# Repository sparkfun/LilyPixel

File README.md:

LilyPad Pixel Board
===================

[*LilyPad Pixel Board (DEV-13264)*](https://www.sparkfun.com/products/13264)

This is a sewable single RGB LEDThe pixel board is equipped with a WS2812. This is an RGB LED with an WS2811 built right into the LED. 
These can be chained together to form a display or an addressable string. 

Repository Contents
-------------------
* **/Hardware** - All Eagle design files (.brd, .sch)
* **/Production** - Test bed files and production panel files

Product Versions
----------------
* [DEV-13264](https://www.sparkfun.com/products/13264)- Version 1.1. Currently live. 
* [DEV-11891](https://www.sparkfun.com/products/11891)- Version 1.0. Retired.

Version History
---------------
* [V_1.1](https://github.com/sparkfun/LilyPixel/tree/V_1.1) - GitHub files version 1.1
* [V_1.0](https://github.com/sparkfun/LilyPixel/tree/V_1.0) - GitHub files version 1.0

License Information
-------------------

This product is _**open source**_! 

Please review the LICENSE.md file for license information. 

If you have any questions or concerns on licensing, please contact techsupport@sparkfun.com.

Distributed as-is; no warranty is given.

- Your friends at SparkFun.

_**Note:** A portion of this sale is given back to Dr. Leah Buechley for continued development and education of e-textiles._

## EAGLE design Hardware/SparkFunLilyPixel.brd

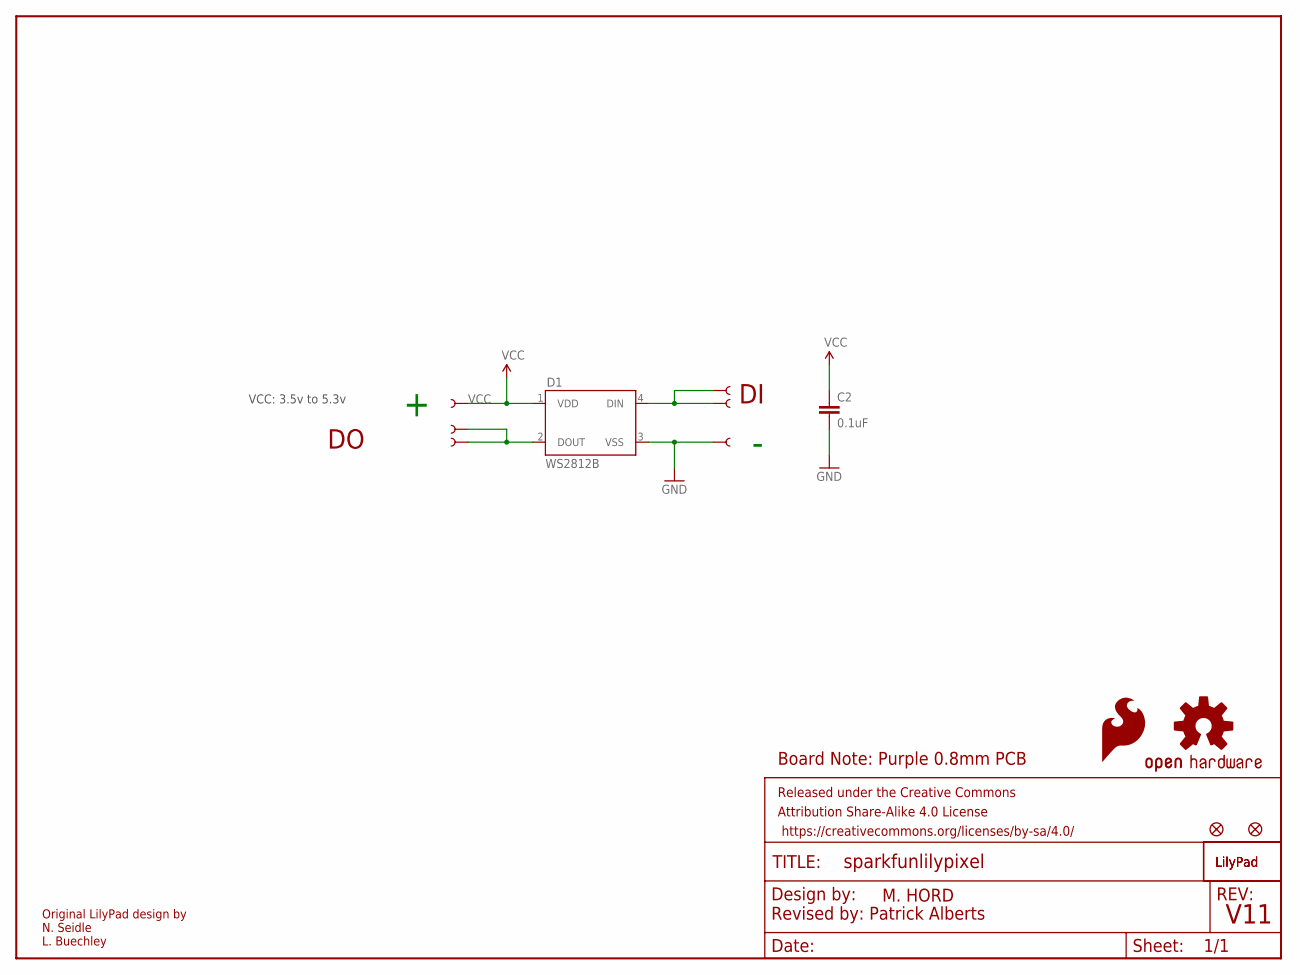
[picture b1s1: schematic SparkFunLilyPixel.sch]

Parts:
C2: 0.1uF; 0603-CAP
D1: WS2812B
FID1, FID2: FIDUCIAL1X2; FIDUCIAL-1X2
FRAME1: FRAME-LETTER; CREATIVE_COMMONS
JP1, JP2, JP3, JP4, JP5, JP6: SEWTAP6; PETAL-SMALL-2SIDE
LOGO1: OSHW-LOGOS; OSHW-LOGO-S
LOGO2: SFE_LOGO_FLAME.1_INCH; SFE_LOGO_FLAME_.1
U$1: LOGO-LPLP; LOGO-LILYPAD
U$8: LOGO-LPL; LOGO-L

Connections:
DI1: D1.4 (DIN), JP5.1, JP6.1
DO1: D1.2 (DOUT), JP1.1, JP2.1
GND: C2.2, D1.3 (VSS), JP3.1
VCC: C2.1, D1.1 (VDD), JP4.1

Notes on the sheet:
M. HORD
V11
Original LilyPad design by N. Seidle L. Buechley
Revised by: Patrick Alberts
VCC: 3.5v to 5.3v
Board Note: Purple 0.8mm PCB

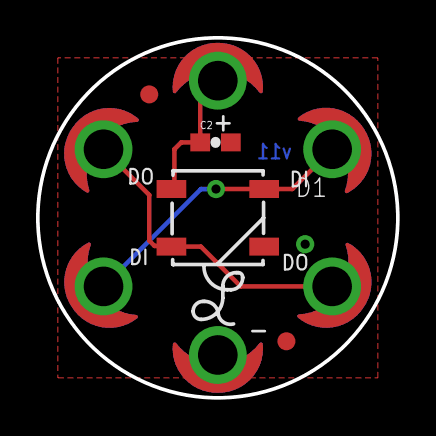
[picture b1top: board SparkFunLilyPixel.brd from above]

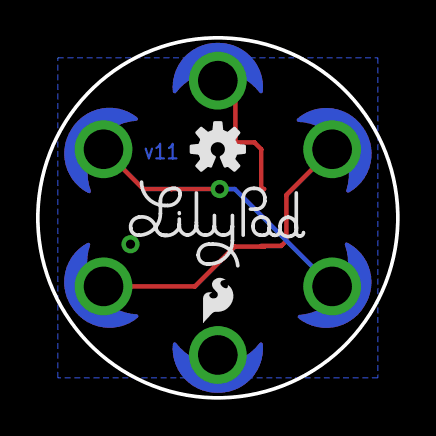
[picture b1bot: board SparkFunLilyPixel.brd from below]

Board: 2 copper layers, 20.0 x 20.0 mm, 15 parts (3 on the bottom side), 4 nets.

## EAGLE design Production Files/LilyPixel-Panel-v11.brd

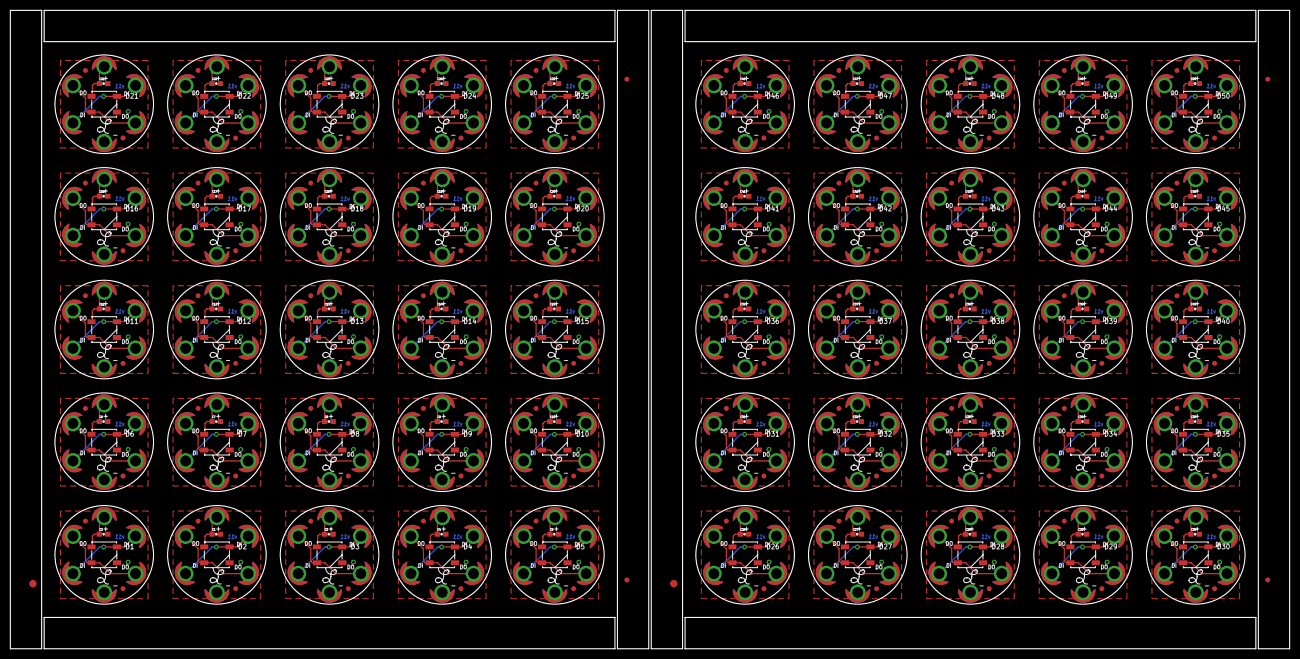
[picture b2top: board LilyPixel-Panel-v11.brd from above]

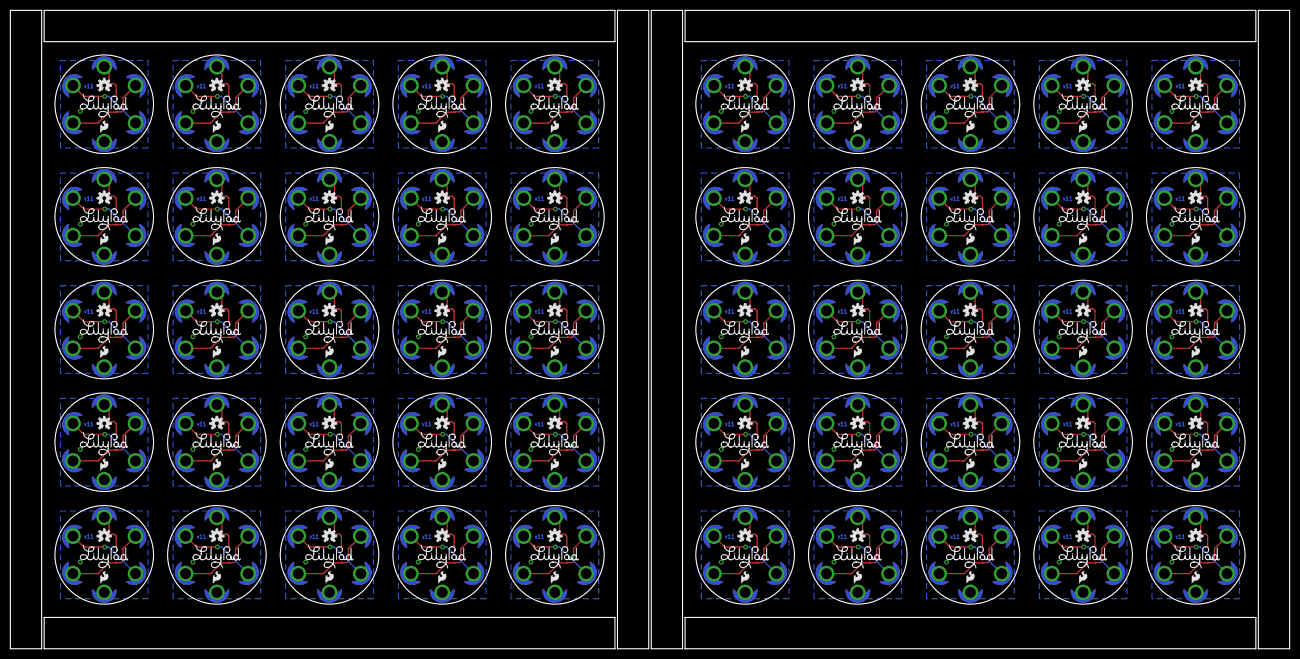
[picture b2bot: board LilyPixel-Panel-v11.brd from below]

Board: 2 copper layers, 259.6 x 129.5 mm, 706 parts (150 on the bottom side), 200 nets.

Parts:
C1, C2, C3, C4, C5, C6, C7, C8, C9, C10, C11, C12, C13, C14, C15, C16, C17, C18, C19, C20, C21, C22, C23, C24, C25, C26, C27, C28, C29, C30, C31, C32, C33, C34, C35, C36, C37, C38, C39, C40, C41, C42, C43, C44, C45, C46, C47, C48, C49, C50: 0.1uF; 0603-CAP
D1, D2, D3, D4, D5, D6, D7, D8, D9, D10, D11, D12, D13, D14, D15, D16, D17, D18, D19, D20, D21, D22, D23, D24, D25, D26, D27, D28, D29, D30, D31, D32, D33, D34, D35, D36, D37, D38, D39, D40, D41, D42, D43, D44, D45, D46, D47, D48, D49, D50: WS2812B
E$1, E$6: FIDUCIAL-1.5X3
E$2, E$3, E$4, E$5: FIDUCIAL-1X2
FID1, FID2, FID3, FID4, FID5, FID6, FID7, FID8, FID9, FID10, FID11, FID12, FID13, FID14, FID15, FID16, FID17, FID18, FID19, FID20, FID21, FID22, FID23, FID24, FID25, FID26, FID27, FID28, FID29, FID30, FID31, FID32, FID33, FID34, FID35, FID36, FID37, FID38, FID39, FID40, FID41, FID42, FID43, FID44, FID45, FID46, FID47, FID48, FID49, FID50, FID51, FID52, FID53, FID54, FID55, FID56, FID57, FID58, FID59, FID60, FID61, FID62, FID63, FID64, FID65, FID66, FID67, FID68, FID69, FID70, FID71, FID72, FID73, FID74, FID75, FID76, FID77, FID78, FID79, FID80, FID81, FID82, FID83, FID84, FID85, FID86, FID87, FID88, FID89, FID90, FID91, FID92, FID93, FID94, FID95, FID96, FID97, FID98, FID99, FID100: FIDUCIAL1X2; FIDUCIAL-1X2
JP1, JP2, JP3, JP4, JP5, JP6, JP7, JP8, JP9, JP10, JP11, JP12, JP13, JP14, JP15, JP16, JP17, JP18, JP19, JP20, JP21, JP22, JP23, JP24, JP25, JP26, JP27, JP28, JP29, JP30, JP31, JP32, JP33, JP34, JP35, JP36, JP37, JP38, JP39, JP40, JP41, JP42, JP43, JP44, JP45, JP46, JP47, JP48, JP49, JP50, JP51, JP52, JP53, JP54, JP55, JP56, JP57, JP58, JP59, JP60, JP61, JP62, JP63, JP64, JP65, JP66, JP67, JP68, JP69, JP70, JP71, JP72, JP73, JP74, JP75, JP76, JP77, JP78, JP79, JP80, JP81, JP82, JP83, JP84, JP85, JP86, JP87, JP88, JP89, JP90, JP91, JP92, JP93, JP94, JP95, JP96, JP97, JP98, JP99, JP100, JP101, JP102, JP103, JP104, JP105, JP106, JP107, JP108, JP109, JP110, JP111, JP112, JP113, JP114, JP115, JP116, JP117, JP118, JP119, JP120, JP121, JP122, JP123, JP124, JP125, JP126, JP127, JP128, JP129, JP130, JP131, JP132, JP133, JP134, JP135, JP136, JP137, JP138, JP139, JP140, JP141, JP142, JP143, JP144, JP145, JP146, JP147, JP148, JP149, JP150, JP151, JP152, JP153, JP154, JP155, JP156, JP157, JP158, JP159, JP160, JP161, JP162, JP163, JP164, JP165, JP166, JP167, JP168, JP169, JP170, JP171, JP172, JP173, JP174, JP175, JP176, JP177, JP178, JP179, JP180, JP181, JP182, JP183, JP184, JP185, JP186, JP187, JP188, JP189, JP190, JP191, JP192, JP193, JP194, JP195, JP196, JP197, JP198, JP199, JP200, JP201, JP202, JP203, JP204, JP205, JP206, JP207, JP208, JP209, JP210, JP211, JP212, JP213, JP214, JP215, JP216, JP217, JP218, JP219, JP220, JP221, JP222, JP223, JP224, JP225, JP226, JP227, JP228, JP229, JP230, JP231, JP232, JP233, JP234, JP235, JP236, JP237, JP238, JP239, JP240, JP241, JP242, JP243, JP244, JP245, JP246, JP247, JP248, JP249, JP250, JP251, JP252, JP253, JP254, JP255, JP256, JP257, JP258, JP259, JP260, JP261, JP262, JP263, JP264, JP265, JP266, JP267, JP268, JP269, JP270, JP271, JP272, JP273, JP274, JP275, JP276, JP277, JP278, JP279, JP280, JP281, JP282, JP283, JP284, JP285, JP286, JP287, JP288, JP289, JP290, JP291, JP292, JP293, JP294, JP295, JP296, JP297, JP298, JP299, JP300: SEWTAP6; PETAL-SMALL-2SIDE
LOGO1, LOGO3, LOGO5, LOGO7, LOGO9, LOGO11, LOGO13, LOGO15, LOGO17, LOGO19, LOGO21, LOGO23, LOGO25, LOGO27, LOGO29, LOGO31, LOGO33, LOGO35, LOGO37, LOGO39, LOGO41, LOGO43, LOGO45, LOGO47, LOGO49, LOGO51, LOGO53, LOGO55, LOGO57, LOGO59, LOGO61, LOGO63, LOGO65, LOGO67, LOGO69, LOGO71, LOGO73, LOGO75, LOGO77, LOGO79, LOGO81, LOGO83, LOGO85, LOGO87, LOGO89, LOGO91, LOGO93, LOGO95, LOGO97, LOGO99: OSHW-LOGOS; OSHW-LOGO-S
LOGO2, LOGO4, LOGO6, LOGO8, LOGO10, LOGO12, LOGO14, LOGO16, LOGO18, LOGO20, LOGO22, LOGO24, LOGO26, LOGO28, LOGO30, LOGO32, LOGO34, LOGO36, LOGO38, LOGO40, LOGO42, LOGO44, LOGO46, LOGO48, LOGO50, LOGO52, LOGO54, LOGO56, LOGO58, LOGO60, LOGO62, LOGO64, LOGO66, LOGO68, LOGO70, LOGO72, LOGO74, LOGO76, LOGO78, LOGO80, LOGO82, LOGO84, LOGO86, LOGO88, LOGO90, LOGO92, LOGO94, LOGO96, LOGO98, LOGO100: SFE_LOGO_FLAME.1_INCH; SFE_LOGO_FLAME_.1
U$1, U$3, U$5, U$7, U$10, U$12, U$14, U$16, U$18, U$20, U$22, U$24, U$26, U$28, U$30, U$32, U$34, U$36, U$38, U$40, U$42, U$44, U$46, U$48, U$50, U$52, U$54, U$56, U$58, U$60, U$62, U$64, U$66, U$68, U$70, U$72, U$74, U$76, U$78, U$80, U$82, U$84, U$86, U$88, U$90, U$92, U$94, U$96, U$98, U$100: LOGO-LPLP; LOGO-LILYPAD
U$2, U$4, U$6, U$8, U$9, U$11, U$13, U$15, U$17, U$19, U$21, U$23, U$25, U$27, U$29, U$31, U$33, U$35, U$37, U$39, U$41, U$43, U$45, U$47, U$49, U$51, U$53, U$55, U$57, U$59, U$61, U$63, U$65, U$67, U$69, U$71, U$73, U$75, U$77, U$79, U$81, U$83, U$85, U$87, U$89, U$91, U$93, U$95, U$97, U$99: LOGO-LPL; LOGO-L

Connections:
DI1: D1.4, JP5.1, JP6.1
DI2: D2.4, JP8.1, JP12.1
DI3: D3.4, JP14.1, JP18.1
DI4: D4.4, JP20.1, JP24.1
DI5: D5.4, JP26.1, JP30.1
DI6: D6.4, JP32.1, JP36.1
DI7: D7.4, JP38.1, JP42.1
DI8: D8.4, JP44.1, JP48.1
DI9: D9.4, JP50.1, JP54.1
DI10: D10.4, JP56.1, JP60.1
DI11: D11.4, JP62.1, JP66.1
DI12: D12.4, JP68.1, JP72.1
DI13: D13.4, JP74.1, JP78.1
DI14: D14.4, JP80.1, JP84.1
DI15: D15.4, JP86.1, JP90.1
DI16: D16.4, JP92.1, JP96.1
DI17: D17.4, JP98.1, JP102.1
DI18: D18.4, JP104.1, JP108.1
DI19: D19.4, JP110.1, JP114.1
DI20: D20.4, JP116.1, JP120.1
DI21: D21.4, JP122.1, JP126.1
DI22: D22.4, JP128.1, JP132.1
DI23: D23.4, JP134.1, JP138.1
DI24: D24.4, JP140.1, JP144.1
DI25: D25.4, JP146.1, JP150.1
DI26: D26.4, JP152.1, JP156.1
DI27: D27.4, JP158.1, JP162.1
DI28: D28.4, JP164.1, JP168.1
DI29: D29.4, JP170.1, JP174.1
DI30: D30.4, JP176.1, JP180.1
DI31: D31.4, JP182.1, JP186.1
DI32: D32.4, JP188.1, JP192.1
DI33: D33.4, JP194.1, JP198.1
DI34: D34.4, JP200.1, JP204.1
DI35: D35.4, JP206.1, JP210.1
DI36: D36.4, JP212.1, JP216.1
DI37: D37.4, JP218.1, JP222.1
DI38: D38.4, JP224.1, JP228.1
DI39: D39.4, JP230.1, JP234.1
DI40: D40.4, JP236.1, JP240.1
DI41: D41.4, JP242.1, JP246.1
DI42: D42.4, JP248.1, JP252.1
DI43: D43.4, JP254.1, JP258.1
DI44: D44.4, JP260.1, JP264.1
DI45: D45.4, JP266.1, JP270.1
DI46: D46.4, JP272.1, JP276.1
DI47: D47.4, JP278.1, JP282.1
DI48: D48.4, JP284.1, JP288.1
DI49: D49.4, JP290.1, JP294.1
DI50: D50.4, JP296.1, JP300.1
DO1: D1.2, JP1.1, JP2.1
DO2: D2.2, JP10.1, JP11.1
DO3: D3.2, JP16.1, JP17.1
DO4: D4.2, JP22.1, JP23.1
DO5: D5.2, JP28.1, JP29.1
DO6: D6.2, JP34.1, JP35.1
DO7: D7.2, JP40.1, JP41.1
DO8: D8.2, JP46.1, JP47.1
DO9: D9.2, JP52.1, JP53.1
DO10: D10.2, JP58.1, JP59.1
DO11: D11.2, JP64.1, JP65.1
DO12: D12.2, JP70.1, JP71.1
DO13: D13.2, JP76.1, JP77.1
DO14: D14.2, JP82.1, JP83.1
DO15: D15.2, JP88.1, JP89.1
DO16: D16.2, JP94.1, JP95.1
DO17: D17.2, JP100.1, JP101.1
DO18: D18.2, JP106.1, JP107.1
DO19: D19.2, JP112.1, JP113.1
DO20: D20.2, JP118.1, JP119.1
DO21: D21.2, JP124.1, JP125.1
DO22: D22.2, JP130.1, JP131.1
DO23: D23.2, JP136.1, JP137.1
DO24: D24.2, JP142.1, JP143.1
DO25: D25.2, JP148.1, JP149.1
DO26: D26.2, JP154.1, JP155.1
DO27: D27.2, JP160.1, JP161.1
DO28: D28.2, JP166.1, JP167.1
DO29: D29.2, JP172.1, JP173.1
DO30: D30.2, JP178.1, JP179.1
DO31: D31.2, JP184.1, JP185.1
DO32: D32.2, JP190.1, JP191.1
DO33: D33.2, JP196.1, JP197.1
DO34: D34.2, JP202.1, JP203.1
DO35: D35.2, JP208.1, JP209.1
DO36: D36.2, JP214.1, JP215.1
DO37: D37.2, JP220.1, JP221.1
DO38: D38.2, JP226.1, JP227.1
DO39: D39.2, JP232.1, JP233.1
DO40: D40.2, JP238.1, JP239.1
DO41: D41.2, JP244.1, JP245.1
DO42: D42.2, JP250.1, JP251.1
DO43: D43.2, JP256.1, JP257.1
DO44: D44.2, JP262.1, JP263.1
DO45: D45.2, JP268.1, JP269.1
DO46: D46.2, JP274.1, JP275.1
DO47: D47.2, JP280.1, JP281.1
DO48: D48.2, JP286.1, JP287.1
DO49: D49.2, JP292.1, JP293.1
DO50: D50.2, JP298.1, JP299.1
GND: C2.2, D1.3, JP3.1
GND1: C1.2, D2.3, JP9.1
GND2: C3.2, D3.3, JP15.1
GND3: C4.2, D4.3, JP21.1
GND4: C5.2, D5.3, JP27.1
GND5: C6.2, D6.3, JP33.1
GND6: C7.2, D7.3, JP39.1
GND7: C8.2, D8.3, JP45.1
GND8: C9.2, D9.3, JP51.1
GND9: C10.2, D10.3, JP57.1
GND10: C11.2, D11.3, JP63.1
GND11: C12.2, D12.3, JP69.1
GND12: C13.2, D13.3, JP75.1
GND13: C14.2, D14.3, JP81.1
GND14: C15.2, D15.3, JP87.1
GND15: C16.2, D16.3, JP93.1
GND16: C17.2, D17.3, JP99.1
GND17: C18.2, D18.3, JP105.1
GND18: C19.2, D19.3, JP111.1
GND19: C20.2, D20.3, JP117.1
GND20: C21.2, D21.3, JP123.1
GND21: C22.2, D22.3, JP129.1
GND22: C23.2, D23.3, JP135.1
GND23: C24.2, D24.3, JP141.1
GND24: C25.2, D25.3, JP147.1
GND25: C26.2, D26.3, JP153.1
GND26: C27.2, D27.3, JP159.1
GND27: C28.2, D28.3, JP165.1
GND28: C29.2, D29.3, JP171.1
GND29: C30.2, D30.3, JP177.1
GND30: C31.2, D31.3, JP183.1
GND31: C32.2, D32.3, JP189.1
GND32: C33.2, D33.3, JP195.1
GND33: C34.2, D34.3, JP201.1
GND34: C35.2, D35.3, JP207.1
GND35: C36.2, D36.3, JP213.1
GND36: C37.2, D37.3, JP219.1
GND37: C38.2, D38.3, JP225.1
GND38: C39.2, D39.3, JP231.1
GND39: C40.2, D40.3, JP237.1
GND40: C41.2, D41.3, JP243.1
GND41: C42.2, D42.3, JP249.1
GND42: C43.2, D43.3, JP255.1
GND43: C44.2, D44.3, JP261.1
GND44: C45.2, D45.3, JP267.1
GND45: C46.2, D46.3, JP273.1
GND46: C47.2, D47.3, JP279.1
GND47: C48.2, D48.3, JP285.1
GND48: C49.2, D49.3, JP291.1
GND49: C50.2, D50.3, JP297.1
VCC: C2.1, D1.1, JP4.1
VCC1: C1.1, D2.1, JP7.1
VCC2: C3.1, D3.1, JP13.1
VCC3: C4.1, D4.1, JP19.1
VCC4: C5.1, D5.1, JP25.1
VCC5: C6.1, D6.1, JP31.1
VCC6: C7.1, D7.1, JP37.1
VCC7: C8.1, D8.1, JP43.1
VCC8: C9.1, D9.1, JP49.1
VCC9: C10.1, D10.1, JP55.1
VCC10: C11.1, D11.1, JP61.1
VCC11: C12.1, D12.1, JP67.1
VCC12: C13.1, D13.1, JP73.1
VCC13: C14.1, D14.1, JP79.1
VCC14: C15.1, D15.1, JP85.1
VCC15: C16.1, D16.1, JP91.1
VCC16: C17.1, D17.1, JP97.1
VCC17: C18.1, D18.1, JP103.1
VCC18: C19.1, D19.1, JP109.1
VCC19: C20.1, D20.1, JP115.1
VCC20: C21.1, D21.1, JP121.1
VCC21: C22.1, D22.1, JP127.1
VCC22: C23.1, D23.1, JP133.1
VCC23: C24.1, D24.1, JP139.1
VCC24: C25.1, D25.1, JP145.1
VCC25: C26.1, D26.1, JP151.1
VCC26: C27.1, D27.1, JP157.1
VCC27: C28.1, D28.1, JP163.1
VCC28: C29.1, D29.1, JP169.1
VCC29: C30.1, D30.1, JP175.1
VCC30: C31.1, D31.1, JP181.1
VCC31: C32.1, D32.1, JP187.1
VCC32: C33.1, D33.1, JP193.1
VCC33: C34.1, D34.1, JP199.1
VCC34: C35.1, D35.1, JP205.1
VCC35: C36.1, D36.1, JP211.1
VCC36: C37.1, D37.1, JP217.1
VCC37: C38.1, D38.1, JP223.1
VCC38: C39.1, D39.1, JP229.1
VCC39: C40.1, D40.1, JP235.1
VCC40: C41.1, D41.1, JP241.1
VCC41: C42.1, D42.1, JP247.1
VCC42: C43.1, D43.1, JP253.1
VCC43: C44.1, D44.1, JP259.1
VCC44: C45.1, D45.1, JP265.1
VCC45: C46.1, D46.1, JP271.1
VCC46: C47.1, D47.1, JP277.1
VCC47: C48.1, D48.1, JP283.1
VCC48: C49.1, D49.1, JP289.1
VCC49: C50.1, D50.1, JP295.1

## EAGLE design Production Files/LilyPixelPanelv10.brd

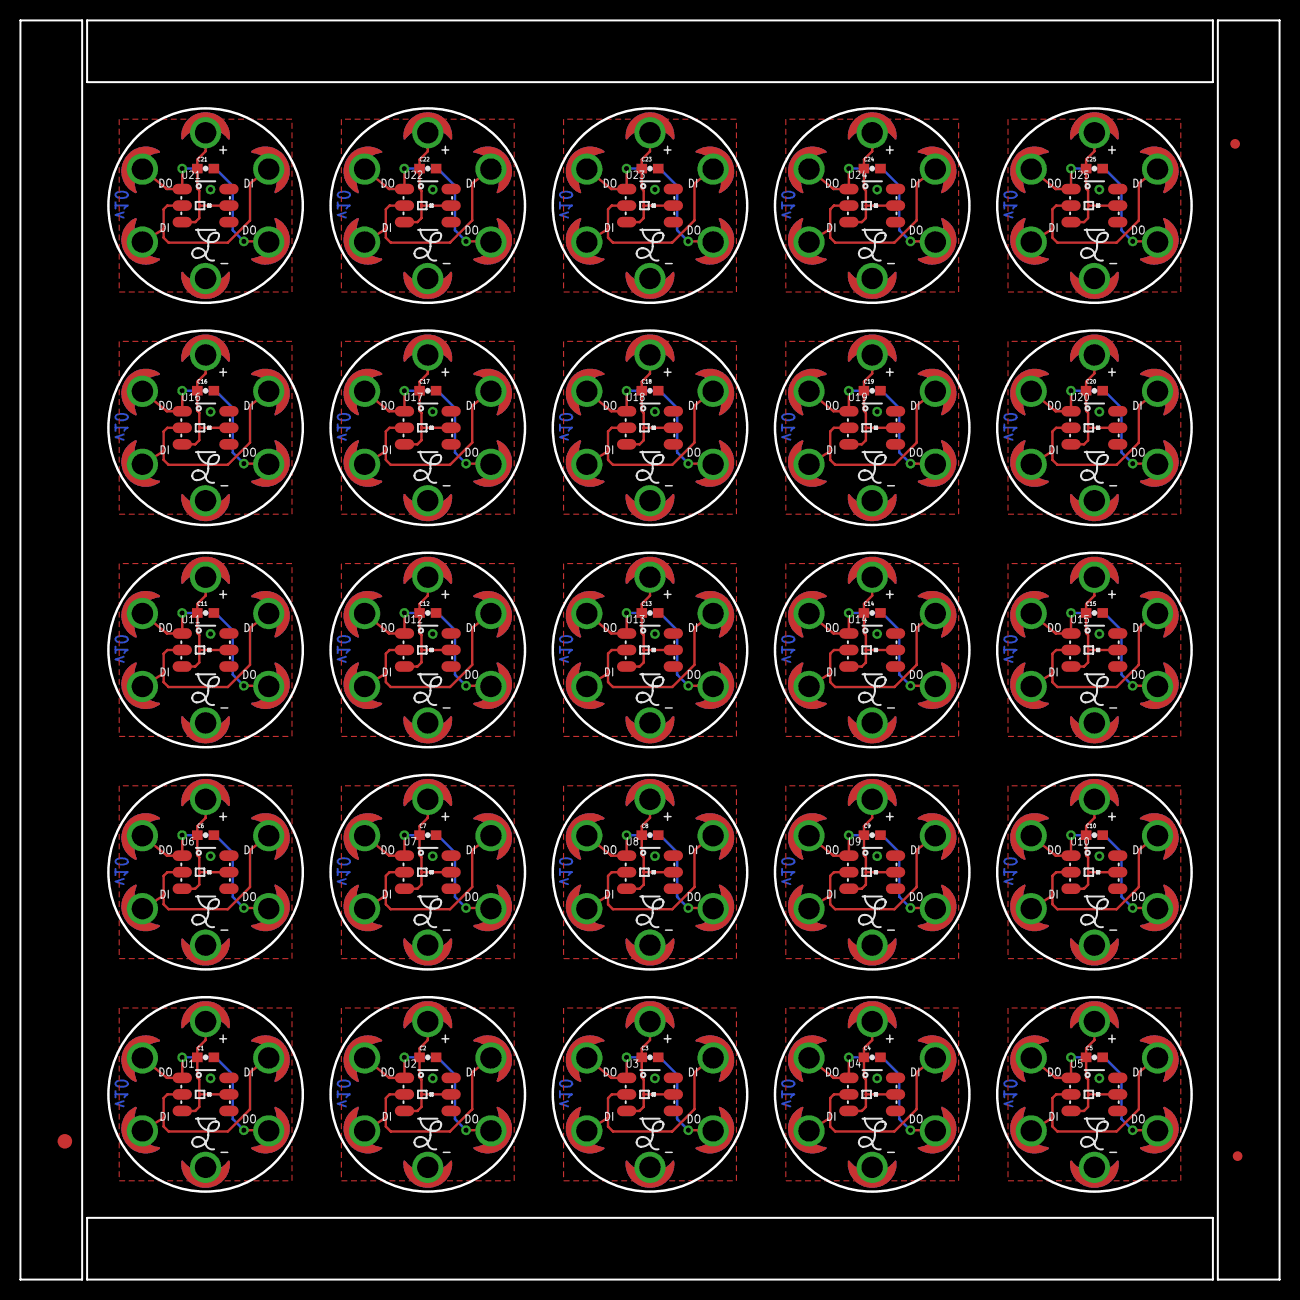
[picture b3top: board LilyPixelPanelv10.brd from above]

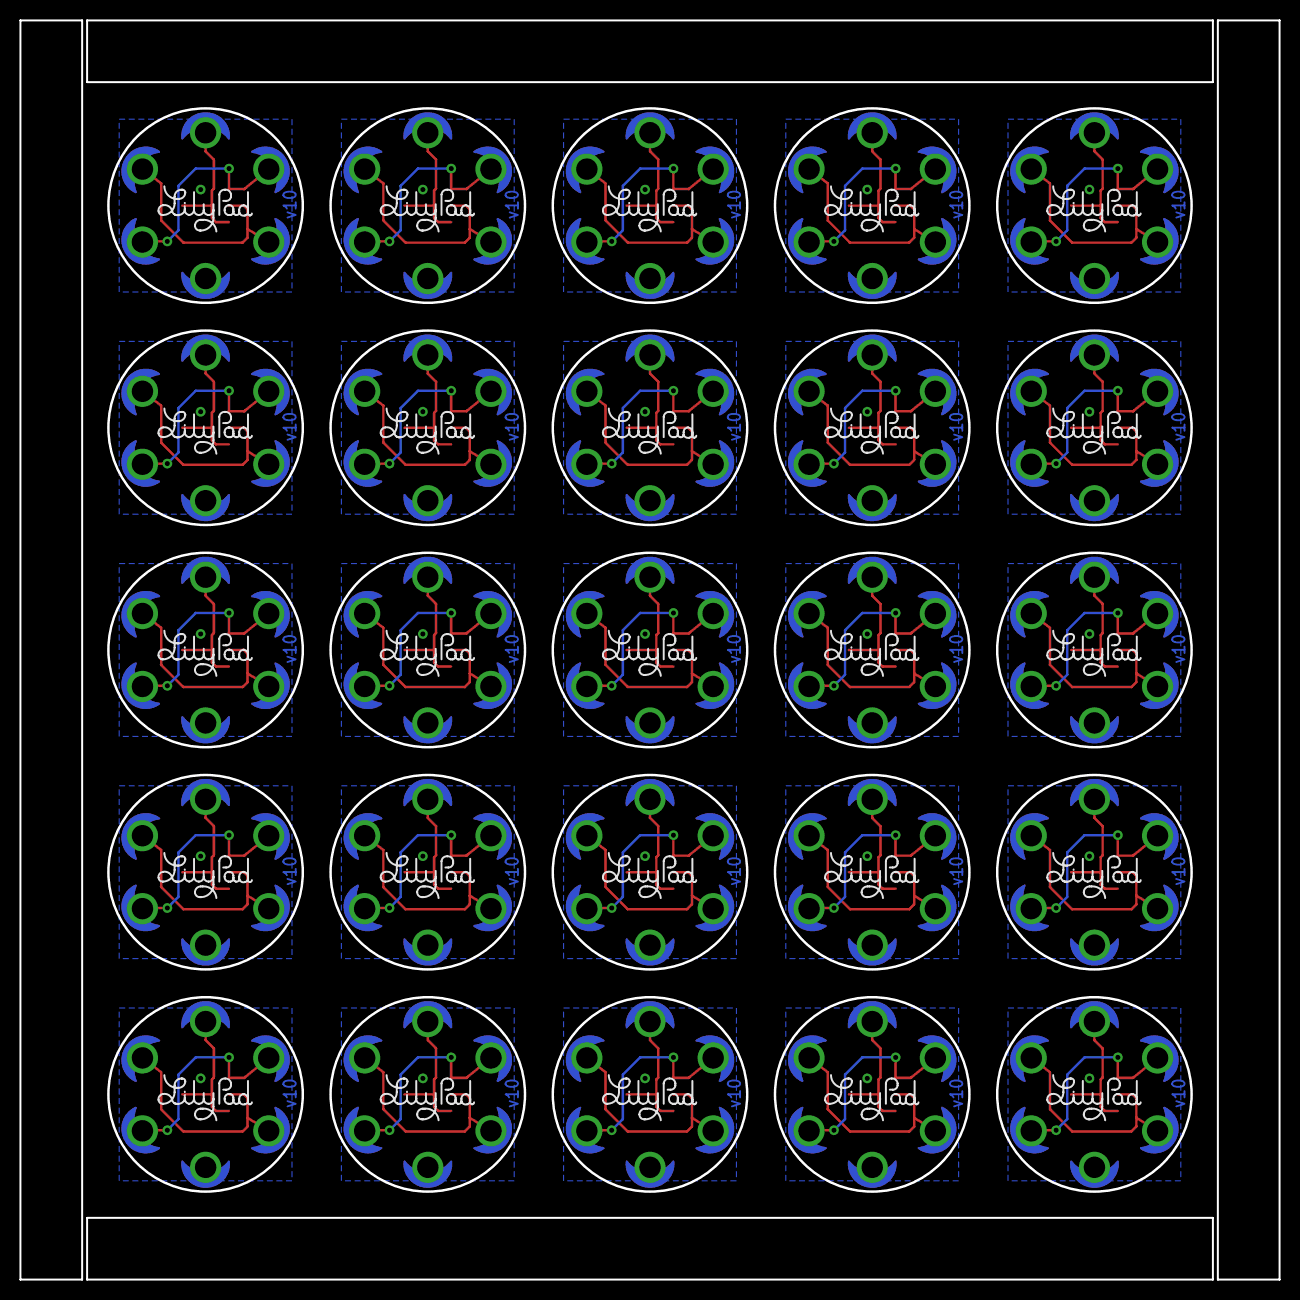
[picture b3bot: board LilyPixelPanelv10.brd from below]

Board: 2 copper layers, 129.5 x 129.5 mm, 253 parts (25 on the bottom side), 100 nets.

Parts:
C1, C2, C3, C4, C5, C6, C7, C8, C9, C10, C11, C12, C13, C14, C15, C16, C17, C18, C19, C20, C21, C22, C23, C24, C25: 0.1uF; 0603-CAP
E$1: FIDUCIAL-1.5X3
E$3, E$6: FIDUCIAL-1X2
U1, U2, U3, U4, U5, U6, U7, U8, U9, U10, U11, U12, U13, U14, U15, U16, U17, U18, U19, U20, U21, U22, U23, U24, U25: WS2811; LED-TRICOLOR-5050-IC
U$1, U$16, U$24, U$32, U$40, U$48, U$56, U$64, U$72, U$80, U$88, U$96, U$104, U$112, U$120, U$128, U$136, U$144, U$152, U$160, U$168, U$176, U$184, U$192, U$200: LOGO-LPLP; LOGO-LILYPAD
U$2, U$3, U$4, U$5, U$6, U$7, U$9, U$10, U$11, U$12, U$13, U$14, U$17, U$18, U$19, U$20, U$21, U$22, U$25, U$26, U$27, U$28, U$29, U$30, U$33, U$34, U$35, U$36, U$37, U$38, U$41, U$42, U$43, U$44, U$45, U$46, U$49, U$50, U$51, U$52, U$53, U$54, U$57, U$58, U$59, U$60, U$61, U$62, U$65, U$66, U$67, U$68, U$69, U$70, U$73, U$74, U$75, U$76, U$77, U$78, U$81, U$82, U$83, U$84, U$85, U$86, U$89, U$90, U$91, U$92, U$93, U$94, U$97, U$98, U$99, U$100, U$101, U$102, U$105, U$106, U$107, U$108, U$109, U$110, U$113, U$114, U$115, U$116, U$117, U$118, U$121, U$122, U$123, U$124, U$125, U$126, U$129, U$130, U$131, U$132, U$133, U$134, U$137, U$138, U$139, U$140, U$141, U$142, U$145, U$146, U$147, U$148, U$149, U$150, U$153, U$154, U$155, U$156, U$157, U$158, U$161, U$162, U$163, U$164, U$165, U$166, U$169, U$170, U$171, U$172, U$173, U$174, U$177, U$178, U$179, U$180, U$181, U$182, U$185, U$186, U$187, U$188, U$189, U$190, U$193, U$194, U$195, U$196, U$197, U$198: SEWTAP6; PETAL-SMALL-2SIDE
U$8, U$15, U$23, U$31, U$39, U$47, U$55, U$63, U$71, U$79, U$87, U$95, U$103, U$111, U$119, U$127, U$135, U$143, U$151, U$159, U$167, U$175, U$183, U$191, U$199: LOGO-LPL; LOGO-L

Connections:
DI: U1.2, U$2.1, U$4.1
DI1: U2.2, U$9.1, U$11.1
DI2: U3.2, U$17.1, U$19.1
DI3: U4.2, U$25.1, U$27.1
DI4: U5.2, U$33.1, U$35.1
DI5: U6.2, U$41.1, U$43.1
DI6: U7.2, U$49.1, U$51.1
DI7: U8.2, U$57.1, U$59.1
DI8: U9.2, U$65.1, U$67.1
DI9: U10.2, U$73.1, U$75.1
DI10: U11.2, U$81.1, U$83.1
DI11: U12.2, U$89.1, U$91.1
DI12: U13.2, U$97.1, U$99.1
DI13: U14.2, U$105.1, U$107.1
DI14: U15.2, U$113.1, U$115.1
DI15: U16.2, U$121.1, U$123.1
DI16: U17.2, U$129.1, U$131.1
DI17: U18.2, U$137.1, U$139.1
DI18: U19.2, U$145.1, U$147.1
DI19: U20.2, U$153.1, U$155.1
DI20: U21.2, U$161.1, U$163.1
DI21: U22.2, U$169.1, U$171.1
DI22: U23.2, U$177.1, U$179.1
DI23: U24.2, U$185.1, U$187.1
DI24: U25.2, U$193.1, U$195.1
DO: U1.1, U$3.1, U$5.1
DO1: U2.1, U$10.1, U$12.1
DO2: U3.1, U$18.1, U$20.1
DO3: U4.1, U$26.1, U$28.1
DO4: U5.1, U$34.1, U$36.1
DO5: U6.1, U$42.1, U$44.1
DO6: U7.1, U$50.1, U$52.1
DO7: U8.1, U$58.1, U$60.1
DO8: U9.1, U$66.1, U$68.1
DO9: U10.1, U$74.1, U$76.1
DO10: U11.1, U$82.1, U$84.1
DO11: U12.1, U$90.1, U$92.1
DO12: U13.1, U$98.1, U$100.1
DO13: U14.1, U$106.1, U$108.1
DO14: U15.1, U$114.1, U$116.1
DO15: U16.1, U$122.1, U$124.1
DO16: U17.1, U$130.1, U$132.1
DO17: U18.1, U$138.1, U$140.1
DO18: U19.1, U$146.1, U$148.1
DO19: U20.1, U$154.1, U$156.1
DO20: U21.1, U$162.1, U$164.1
DO21: U22.1, U$170.1, U$172.1
DO22: U23.1, U$178.1, U$180.1
DO23: U24.1, U$186.1, U$188.1
DO24: U25.1, U$194.1, U$196.1
GND: C1.2, U1.6, U$7.1
GND1: C2.2, U2.6, U$14.1
GND2: C3.2, U3.6, U$22.1
GND3: C4.2, U4.6, U$30.1
GND4: C5.2, U5.6, U$38.1
GND5: C6.2, U6.6, U$46.1
GND6: C7.2, U7.6, U$54.1
GND7: C8.2, U8.6, U$62.1
GND8: C9.2, U9.6, U$70.1
GND9: C10.2, U10.6, U$78.1
GND10: C11.2, U11.6, U$86.1
GND11: C12.2, U12.6, U$94.1
GND12: C13.2, U13.6, U$102.1
GND13: C14.2, U14.6, U$110.1
GND14: C15.2, U15.6, U$118.1
GND15: C16.2, U16.6, U$126.1
GND16: C17.2, U17.6, U$134.1
GND17: C18.2, U18.6, U$142.1
GND18: C19.2, U19.6, U$150.1
GND19: C20.2, U20.6, U$158.1
GND20: C21.2, U21.6, U$166.1
GND21: C22.2, U22.6, U$174.1
GND22: C23.2, U23.6, U$182.1
GND23: C24.2, U24.6, U$190.1
GND24: C25.2, U25.6, U$198.1
VCC: C1.1, U1.3, U1.5, U$6.1
VCC1: C2.1, U2.3, U2.5, U$13.1
VCC2: C3.1, U3.3, U3.5, U$21.1
VCC3: C4.1, U4.3, U4.5, U$29.1
VCC4: C5.1, U5.3, U5.5, U$37.1
VCC5: C6.1, U6.3, U6.5, U$45.1
VCC6: C7.1, U7.3, U7.5, U$53.1
VCC7: C8.1, U8.3, U8.5, U$61.1
VCC8: C9.1, U9.3, U9.5, U$69.1
VCC9: C10.1, U10.3, U10.5, U$77.1
VCC10: C11.1, U11.3, U11.5, U$85.1
VCC11: C12.1, U12.3, U12.5, U$93.1
VCC12: C13.1, U13.3, U13.5, U$101.1
VCC13: C14.1, U14.3, U14.5, U$109.1
VCC14: C15.1, U15.3, U15.5, U$117.1
VCC15: C16.1, U16.3, U16.5, U$125.1
VCC16: C17.1, U17.3, U17.5, U$133.1
VCC17: C18.1, U18.3, U18.5, U$141.1
VCC18: C19.1, U19.3, U19.5, U$149.1
VCC19: C20.1, U20.3, U20.5, U$157.1
VCC20: C21.1, U21.3, U21.5, U$165.1
VCC21: C22.1, U22.3, U22.5, U$173.1
VCC22: C23.1, U23.3, U23.5, U$181.1
VCC23: C24.1, U24.3, U24.5, U$189.1
VCC24: C25.1, U25.3, U25.5, U$197.1

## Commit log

2013-06-03 Initial commit for protos.
2013-07-24 Update to v10 for release
2013-07-30 created panel
    Created normal sized panel. This will not go any larger, too flimsy.
2013-07-30 changed panel filename
2013-12-12 Updating README
2014-10-07 replaced led package
2014-10-29 Fixed Shematic, full trace re route
2014-10-30 Trace Cleanup
2014-11-04 LED/Silk Orientation
    Fixed the orientation of the silk, LED and petals.
    Added Sparkfun Flame
2014-11-24 Re assigned Petals, full complete re route.
2014-12-03 Fixed qc checklist problems
2015-01-06 Fixed polarity indicator on LED
2015-01-06 Fixed polarity indicator for Ws2812b
2015-01-12 added regular fiducials
2015-01-12 created panel v11
2015-01-12 made it a giant
2015-07-27 Updating README, adding .git file, adding License
2015-07-27 Update README.md
    Fixing formatting

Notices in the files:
parts and their libraries:
SparkFun-LED: Licensing: CC v3.0 Share-Alike You are welcome to use this library for commercial purposes.
SparkFun-Aesthetics: Released under the Creative Commons Attribution Share-Alike 4.0 License
SparkFun-Aesthetics: https://creativecommons.org/licenses/by-sa/4.0
